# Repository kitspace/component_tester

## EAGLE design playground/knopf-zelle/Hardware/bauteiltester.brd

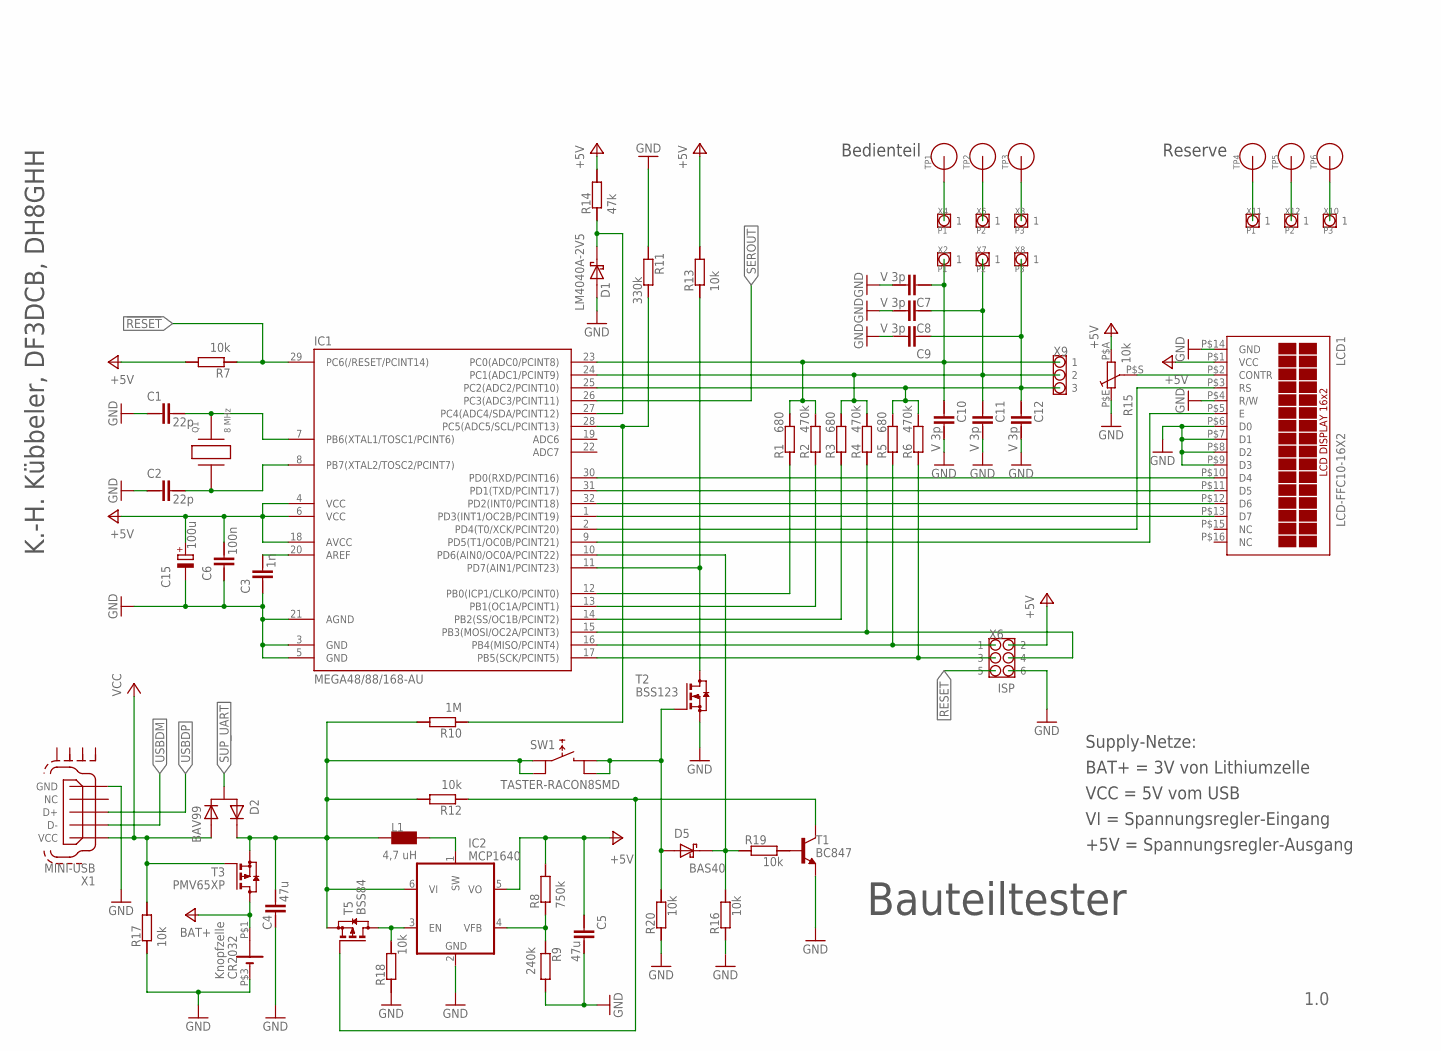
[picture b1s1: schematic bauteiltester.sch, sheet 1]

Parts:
BAT1: CR2032
C1, C2: 22p; C0805
C3: 1n; C0805
C4, C5: 47u; C0805
C6: 100n; C0805
C7, C8, C9, C10, C11, C12: V 3p; C0603
C15: 100u; D/7343-31W
D1: LM4040A-2V5; SOT23
D2: BAV99; SOT23
D5: BAS40; SOT23
IC1: MEGA48/88/168-AU; TQFP32-08
IC2: MCP1640; SOT23-6
L1: 4,7 uH; L1210
LCD1: LCD-FFC10-16X2; FFC_14P_1MM_TOP
Q1: 8 MHz; HC49UP
R1, R3, R5: 680; R0805
R2, R4, R6: 470k; R0805
R7, R12, R13, R16, R17, R18, R19, R20: 10k; R0805
R8: 750k; R0805
R9: 240k; R0805
R10: 1M; R0805
R11: 330k; R0805
R14: 47k; R0805
R15: 10k; POTI_ACP6-SMD
SW1: TASTER-RACON8SMD
T1: BC847; SOT23
T2: BSS123; SOT23
T3: PMV65XP; SOT23
T5: BSS84; SOT23
TP1, TP2, TP3, TP4, TP5, TP6: SMD-PAD_0.2X0.2; PAD_0.2X0.2
X1: MINI-USB; MINI-USB-B5
X2: P1; STIFT
X3, X10: P3; STIFT_WINKL_SMD
X4, X11: P1; STIFT_WINKL_SMD
X5, X12: P2; STIFT_WINKL_SMD
X6: ISP; WANNE6_PCBKANTE
X7: P2; STIFT
X8: P3; STIFT
X9: STIFTLEISTE_2,54MM_1X3_WI-SMD

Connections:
!RESET: IC1.29 (PC6(/RESET/PCINT14)), R7.1, X6.P$5 (5)
+5V: C5.1, C6.2, C15.+, IC1.4 (VCC), IC1.6 (VCC), IC1.18 (AVCC), IC2.5 (VO), LCD1.P$1 (VCC), R7.2, R8.2, R13.2, R14.2, R15.P$A (A), X6.P$2 (2)
BAT+: BAT1.P$1 (+), T3.3 (D); also elsewhere on the board
GND: BAT1.P$3 (-), C1.1, C2.1, C3.1, C4.2, C5.2, C6.1, C7.2, C8.2, C9.2, C10.2, C11.2, C12.2, C15.-, D1.2 (ANODE), IC1.3 (GND), IC1.5 (GND), IC1.21 (AGND), IC2.2 (GND), LCD1.P$4 (R/W), LCD1.P$6 (D0), LCD1.P$7 (D1), LCD1.P$8 (D2), LCD1.P$9 (D3), LCD1.P$14 (GND), R9.2, R11.1, R15.P$E (E), R16.1, R17.1, R18.1, R20.2, T1.2 (E), T2.2 (S), X1.5 (GND), X6.P$6 (6); also elsewhere on the board
MISO: IC1.16 (PB4(MISO/PCINT4)), R5.1, X6.P$1 (1)
MOSI: IC1.15 (PB3(MOSI/OC2A/PCINT3)), R4.1, X6.P$4 (4)
unnamed: IC1.30 (PD0(RXD/PCINT16)), LCD1.P$10 (D4)
unnamed: IC1.31 (PD1(TXD/PCINT17)), LCD1.P$11 (D5)
unnamed: IC1.32 (PD2(INT0/PCINT18)), LCD1.P$12 (D6)
unnamed: IC2.4 (VFB), R8.1, R9.1
unnamed: D5.1 (ANODE), R20.1, SW1.P$2 (2), SW1.P$4 (4), T2.1 (G)
unnamed: C3.2, IC1.20 (AREF)
unnamed: IC1.1 (PD3(INT1/OC2B/PCINT19)), LCD1.P$13 (D7)
unnamed: IC1.9 (PD5(T1/OC0B/PCINT21)), LCD1.P$5 (E)
unnamed: IC1.12 (PB0(ICP1/CLKO/PCINT0)), R1.1
unnamed: C1.2, IC1.7 (PB6(XTAL1/TOSC1/PCINT6)), Q1.2
unnamed: C2.2, IC1.8 (PB7(XTAL2/TOSC2/PCINT7)), Q1.1
unnamed: IC1.13 (PB1(OC1A/PCINT1)), R2.1
unnamed: IC1.14 (PB2(SS/OC1B/PCINT2)), R3.1
unnamed: R19.1, T1.1 (B)
unnamed: IC2.3 (EN), R18.2, T5.3 (D)
unnamed: IC1.2 (PD4(T0/XCK/PCINT20)), LCD1.P$3 (RS)
unnamed: IC2.1 (SW), L1.2
unnamed: IC1.28 (PC5(ADC5/SCL/PCINT13)), R10.1, R11.2
unnamed: LCD1.P$2 (CONTR), R15.P$S (S)
unnamed: IC1.11 (PD7(AIN1/PCINT23)), R13.1, T2.3 (D)
unnamed: R12.1, T1.3 (C), T5.1 (G)
unnamed: D1.1 (KATHODE), IC1.27 (PC4(ADC4/SDA/PCINT12)), R14.1
PAD1: C7.1, C10.1, IC1.23 (PC0(ADC0/PCINT8)), R1.2, R2.2, X2.1, X9.P$1 (1)
PAD2: C8.1, C11.1, IC1.24 (PC1(ADC1/PCINT9)), R3.2, R4.2, X7.1, X9.P$2 (2)
PAD3: C9.1, C12.1, IC1.25 (PC2(ADC2/PCINT10)), R5.2, R6.2, X8.1, X9.P$3 (3)
PD6: D5.3 (KATHODE), IC1.10 (PD6(AIN0/OC0A/PCINT22)), R16.2, R19.2
SCK: IC1.17 (PB5(SCK/PCINT5)), R6.1, X6.P$3 (3)
SEG1: TP1.P$1, TP4.P$1, X4.P$1, X11.P$1
SEG2: TP2.P$1, TP5.P$1, X5.P$1, X12.P$1
SEG3: TP3.P$1, TP6.P$1, X3.P$1, X10.P$1
SEROUT: IC1.26 (PC3(ADC3/PCINT11)); also elsewhere on the board
SUP_UART: D2.3 (A1/K2); also elsewhere on the board
USBDM: X1.2 (D-); also elsewhere on the board
USBDP: X1.3 (D+); also elsewhere on the board
VCC: D2.1 (A2), R17.2, T3.1 (G), X1.1 (VCC); also elsewhere on the board
VI: C4.1, D2.2 (K1), IC2.6 (VI), L1.1, R10.2, R12.2, SW1.P$1 (1), SW1.P$3 (3), T3.2 (S), T5.2 (S)

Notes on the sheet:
Bauteiltester
Knopfzelle
CR2032
Bedienteil
Supply-Netze:
+5V = Spannungsregler-Ausgang
VCC = 5V vom USB
VI = Spannungsregler-Eingang
BAT+ = 3V von Lithiumzelle
Reserve
K.-H. Kübbeler, DF3DCB, DH8GHH

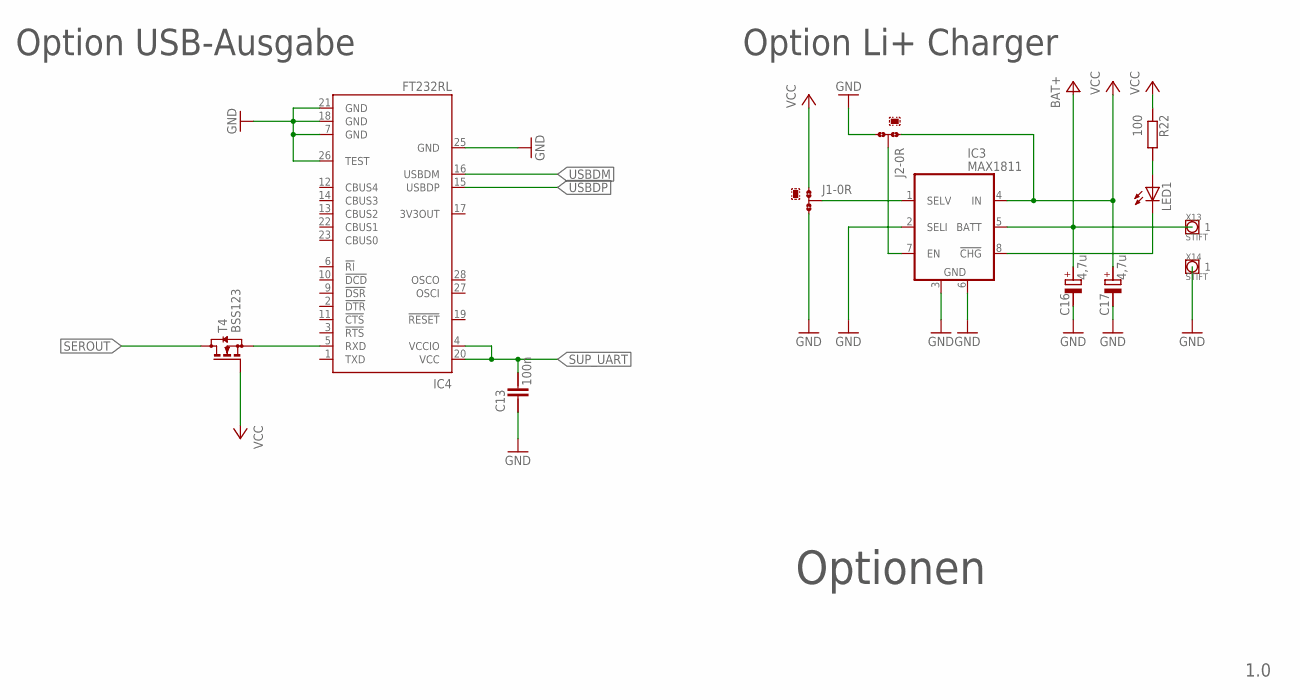
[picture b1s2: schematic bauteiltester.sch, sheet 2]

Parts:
C13: 100n; C0805
C16, C17: 4,7u; C-TAN_A
IC3: MAX1811; SO08
IC4: FT232RL; SSOP28
J1, J2: 0R-JUMPA; A0R-JMP
LED1: LEDCHIP-LED0805; CHIP-LED0805
R22: 100; R0805
T4: BSS123; SOT23
X13, X14: STIFT

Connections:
BAT+: C16.+ (PLUS), IC3.5 (BATT), X13.1; also elsewhere on the board
GND: C13.1, C16.- (MINUS), C17.- (MINUS), IC3.2 (SELI), IC3.3 (GND), IC3.6 (GND1), IC4.7 (GND), IC4.18 (GND), IC4.21 (GND), IC4.25 (GND), IC4.26 (TEST), J1.3, J2.3, X14.1; also elsewhere on the board
unnamed: IC3.7 (EN), J2.2
unnamed: IC3.1 (SELV), J1.2
unnamed: IC3.8 (!CHG), LED1.C
unnamed: LED1.A, R22.2
unnamed: IC4.5 (RXD), T4.2 (S)
SEROUT: T4.3 (D); also elsewhere on the board
SUP_UART: C13.2, IC4.4 (VCCIO), IC4.20 (VCC); also elsewhere on the board
USBDM: IC4.16 (USBDM); also elsewhere on the board
USBDP: IC4.15 (USBDP); also elsewhere on the board
VCC: C17.+ (PLUS), IC3.4 (IN), J1.1, J2.1, R22.1, T4.1 (G); also elsewhere on the board

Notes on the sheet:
Optionen
Option USB-Ausgabe
Option Li+ Charger

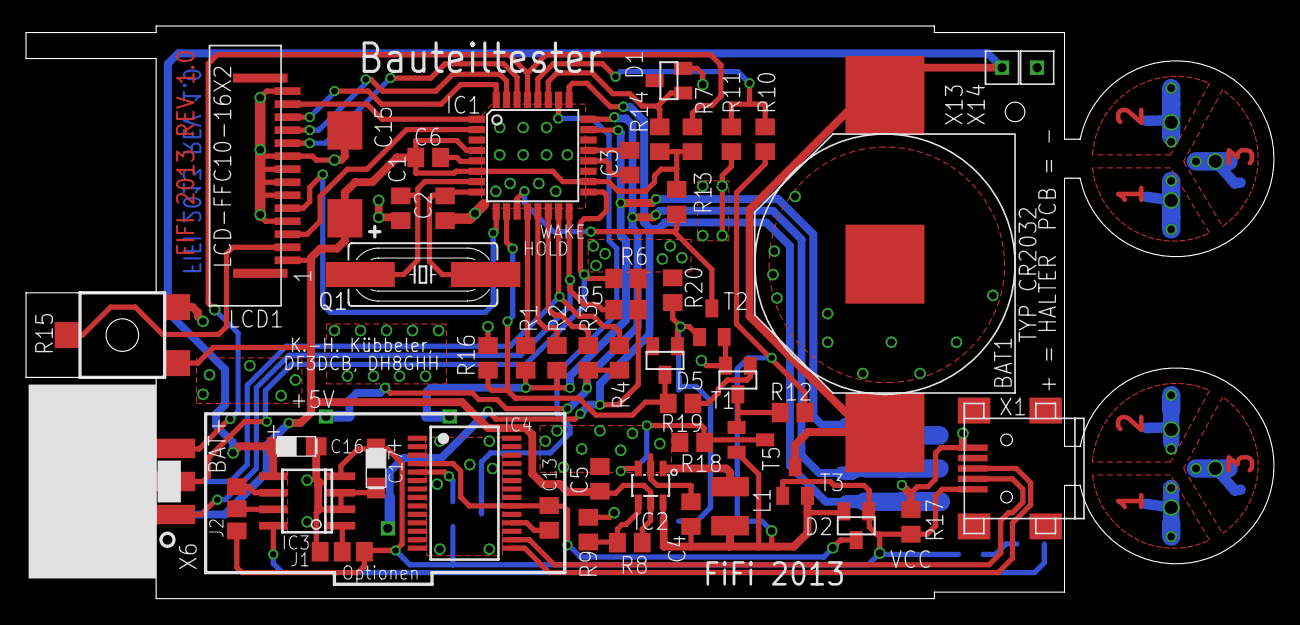
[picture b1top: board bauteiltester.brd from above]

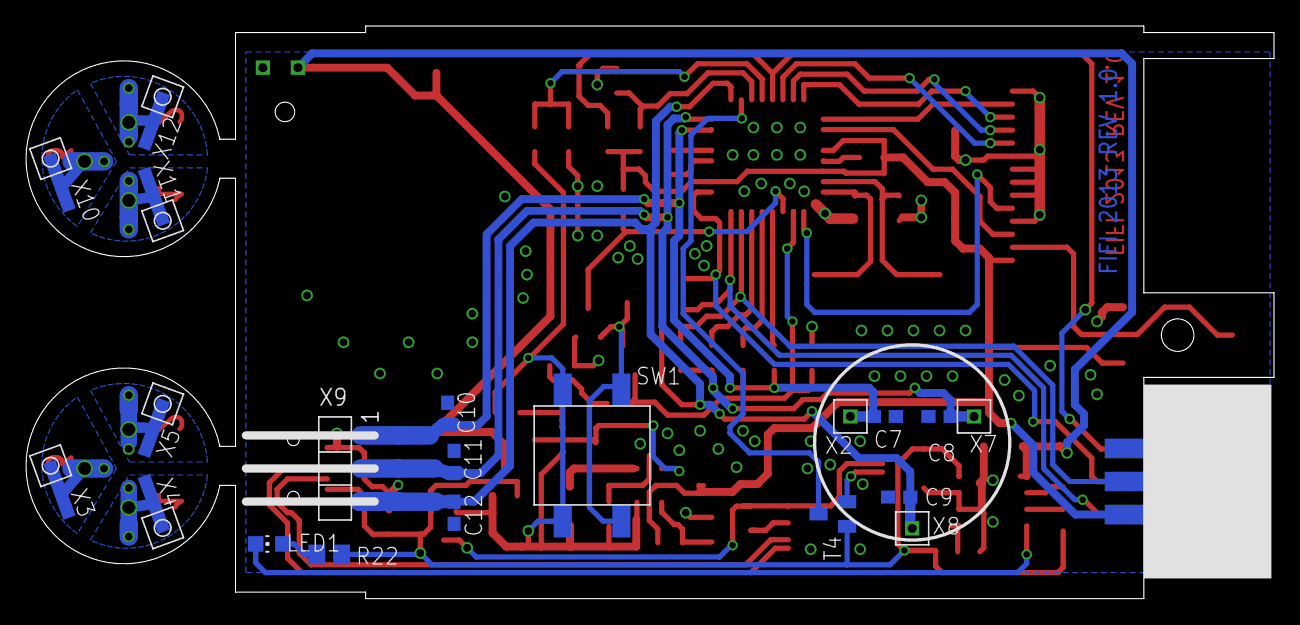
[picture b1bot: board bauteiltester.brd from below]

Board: 2 copper layers, 95.9 x 44.0 mm, 77 parts (26 on the bottom side), 47 nets.

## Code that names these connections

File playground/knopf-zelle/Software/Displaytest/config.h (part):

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#define ADC_PORT PORTC
#define ADC_DDR DDRC
#define ADC_PIN PINC
#define TP1 PC0
#define TP2 PC1
#define TP3 PC2
// Port pin for external Voltage measurement (zener voltage extension)
#define TPext PC3
// Port pin for 2.5V precision reference used for VCC check (optional)
#define TPREF PC4
// Port pin for Battery voltage measuring
#define TPBAT PC5

// setting for voltage devider of Batterie voltage measurement 10K and 3.3k
#ifndef BAT_NUMERATOR
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#define ON_DDR DDRD
#define ON_PORT PORTD
#define ON_PIN_REG PIND
#define ON_PIN PD6      //Pin, must be switched to high to switch power on

#ifdef STRIP_GRID_BOARD
// Strip Grid board version
#define RST_PIN PD0     //Pin, is switched to low, if push button is pressed
#else
// normal layout version
#define RST_PIN PD7     //Pin, is switched to low, if push button is pressed
#endif


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*/
//#define SWUART_INVERT

#define TxD PC3	//TxD-Pin of Software-UART; must be at Port C !
#ifdef WITH_UART
 #define TXD_MSK (1<<TxD)
#else
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
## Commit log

2018-04-19 Work on schematic
2018-04-19 Schema schemaaa
2018-04-19 Move hardware into kicad dir
2018-04-19 Add software
2018-04-19 Run clang-format on software
2018-04-26 Work on svg
2018-04-27 Work on drawings
2018-04-27 Start panelizing
2018-04-28 Work on panelization
2018-04-28 Work on drills
2018-04-28 Panelize the whole thing, rat-bites and all
2018-04-28 Start working on pads
2018-04-28 Try out button and add logo
2018-06-09 Adjust logo url
2018-06-09 Adjust logo text some more
2018-06-09 Import eagle project from o28 fifi bauteiltester
2018-06-09 Add drawings back into pcb
2018-06-10 Fix some schematic eagle import oddities
2018-06-11 Add .bak and .bck to gitignore
2018-06-13 Switch resistors and caps to 0201 where possible
2018-06-14 Switch atemega to smaller footprint
2018-06-14 Switch battery holder footprint
2018-06-14 Add OLED footprint
2018-06-14 Add test pads bottom footprint
2018-06-14 Connect up test pads
2018-06-14 Sort out ground net
2018-06-14 Remove all the ground labels and zones
2018-06-14 Remove all vias
2018-06-14 Sort out power nets/labels
2018-06-15 Import Adafruit OLED breakout
2018-06-15 Switch 0201 footprints for 0402
2018-06-15 Switch out crystal oscillator footprint
2018-06-15 Switch button footprint
2018-06-15 Flip the board and begin placing
2018-06-15 Use hierplace to re-arrange footprints
2018-06-15 Continue placing
2018-06-15 Change USB footprint
2018-06-15 Reduce atmega decoupling cap to 10uF
2018-06-15 Use panasonic evq for tactile switch
2018-06-15 Work on placement
2018-06-15 Make all schematic references and values visible
2018-06-15 Remove unnecessary stuff from OLED circuitry
2018-06-15 Add drawings of inner edges to help with layout
2018-06-16 Adjust pads placement tonot interfere with screen
2018-06-16 Work on placing components
2018-06-16 Switch back to 0201s and continue placing
2018-06-16 Set up design rules and test out routing a bit
2018-06-16 Do some routing
2018-06-16 Make ISP header a pogo pin one
2018-06-17 Adjust layers, make sure ISP through holes have copper
2018-06-17 Work on placing/routing
2018-06-17 Cut out precision voltage reference
2018-06-17 Switch some transistors for smaller footprints
2018-06-17 Route some more
2018-06-19 Place and route
2018-06-19 Route stuff
2018-10-08 Remove all kicad-4 schematic libs
2018-10-08 Remove tags from eagle exported footprints
2020-09-11 Add datasheets and playground directories

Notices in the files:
playground/knopf-zelle/Software/Displaytest/config.h:
CC0 defines the capacity of empty terminal pins 1 & 3 without cable
define CC0 36
define C_NULL CC0+CABLE_CAP+(COMP_SLEW1 / (CC0 + CABLE_CAP + COMP_SLEW2))
define CC0 27
